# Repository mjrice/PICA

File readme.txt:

PICA

Power, Interface, and Control Adapter

An Arduino Mega shield for reprap machines

Based in part on RAMPS by Johnny Russell

Power

* 5x20mm replaceable fuse input 

* 12V to 24V input with on-board 12V buck converter for systems with both 24V and 12V devices

* Five separate MOSFET outputs:

1 High power (15A, up to 24V)
2 Medium power (6A, up to 24V)
2 Low power (2A, 12V)

* Plus 1 SSR output (SPST) capable of 240VAC/5A (more with heatsink)

Monitoring 

* four thermistor inputs
* six endstop inputs

Interface

* LCD interface (SMART LCD controller pinout)
* I2C, 2xSerial, 3xPWM, and auxiliary DC power output connections
* Five Pololu stepper motor driver sockets (A4988 or DRV8825)

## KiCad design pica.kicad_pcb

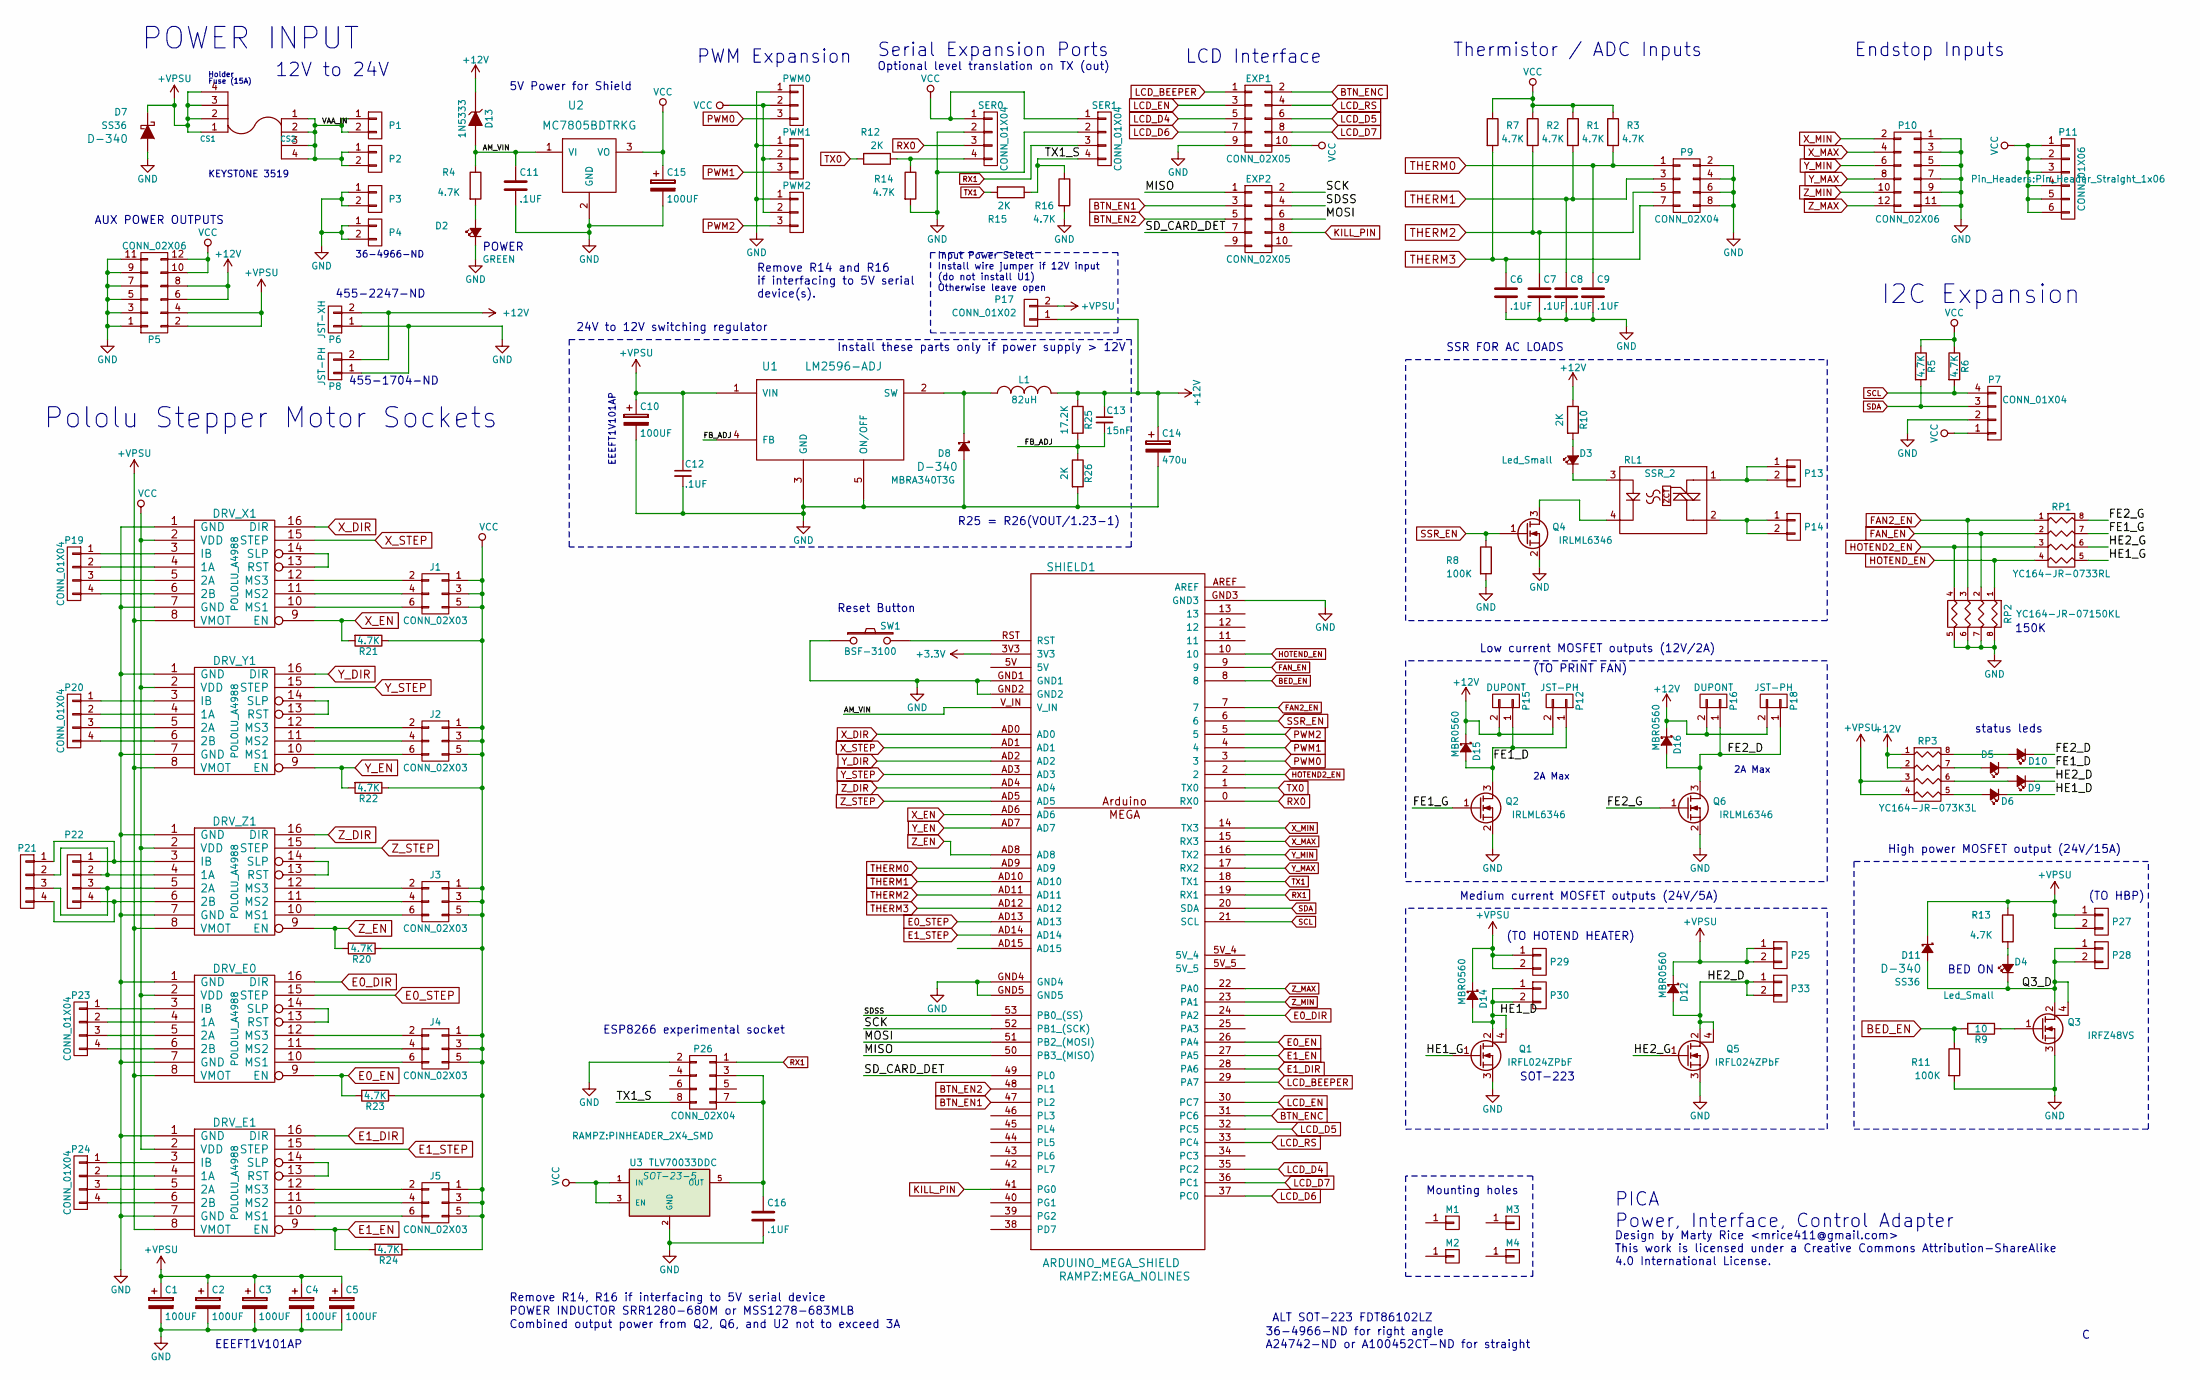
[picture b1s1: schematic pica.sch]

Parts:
C1, C2, C3, C4, C5, C10, C15: 100UF; c_elec_6.3x5.8
C6, C7, C8, C9, C11, C12, C16: .1UF; C_0805_HandSoldering
C13: 15nF; C_0805_HandSoldering
C14: 470u; C_Radial_D10_L13_P5
CS1, CS2: FUSE_CLIP_5x20; FUSE_CLIP_D_5x20
D2: GREEN; LED_1206
D3, D4, D5, D6, D9, D10: Led_Small; LED_1206
D7, D11: SS36; SMA_Handsoldering
D8: MBRA340T3G; SMA_Handsoldering
D12, D14, D15, D16: MBR0560; SOD-123
D13: 1N5333; Diode_Horizontal
DRV_E0, DRV_E1: POLOLU_A4988; SWDIP8_.6W
DRV_X1: POLOLU_A4988; SWDIP8_.6W
DRV_Y1: POLOLU_A4988; SWDIP8_.6W
DRV_Z1: POLOLU_A4988; SWDIP8_.6W
EXP1, EXP2: CONN_02X05; IDC_Header_Straight_10pins
J1, J2, J3, J4, J5: CONN_02X03; DIP-6_0_ELL
L1: 82uH; RH127
M1, M2, M3, M4: CONN_01X01; MHOLE125
P1, P2, P3, P4: 36-4966-ND; SPADE_CONN_RT
P5, P10: CONN_02X06; Pin_Header_Straight_2x06
P6: JST-XH; JST_XH_2POS
P7, P19, P20, P21, P22, P23, P24: CONN_01X04; Pin_Header_Straight_1x04
P8, P12, P18: JST-PH; JST_PH_2POS
P9: CONN_02X04; Pin_Header_Straight_2x04
P11: CONN_01X06; Pin_Header_Straight_1x06
P13, P14, P25, P27, P28, P29, P30, P33: CONN_01X02; SPACE_CONN_VERT
P15, P16: DUPONT; Pin_Header_Straight_1x02
P17: CONN_01X02; Pin_Header_Straight_1x02
P26: CONN_02X04; PINHEADER_2X4_SMD
PWM0, PWM1, PWM2: CONN_01X03; Pin_Header_Straight_1x03
Q1, Q5: IRFL024ZPbF; SOT-223
Q2, Q4, Q6: IRLML6346; SOT-23_Handsoldering
Q3: IRFZ48VS; TO-263-3Lead
R1, R2, R3, R4, R5, R6, R7, R13, R14, R16, R20, R21, R22, R23, R24: 4.7K; R_0805_HandSoldering
R8, R11: 100K; R_0805_HandSoldering
R9: 10; R_0805_HandSoldering
R10, R12, R15, R26: 2K; R_0805_HandSoldering
R25: 17.2K; R_0805_HandSoldering
RL1: SSR_2; I4-PAC
RP1: YC164-JR-0733RL; RESARY_4_CTS_744
RP2: YC164-JR-07150KL; RESARY_4_CTS_744
RP3: YC164-JR-073K3L; RESARY_4_CTS_744
SER0, SER1: CONN_01X04; Pin_Header_Straight_1x04
SHIELD1: ARDUINO_MEGA_SHIELD; MEGA_NOLINES
SW1: BSF-3100; BSF_RT
U1: LM2596-ADJ; TO-263-5Lead
U2: MC7805BDTRKG; TO-252-2Lead
U3: TLV70033DDC; SOT-23-5

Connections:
+3V3: SHIELD1.3V3
+12V: C13.1, C14.1, D13.1 (K), D15.1 (K), D16.1 (K), L1.2, P5.6, P5.8, P6.2, P8.2, P12.2, P15.2, P16.2, P17.1, P18.2, R10.1, R25.1, RP3.1, RP3.2
+VPSU: C1.1, C2.1, C3.1, C4.1, C5.1, C10.1, C12.1, CS1.1, CS1.2, CS1.3, CS1.4, D7.1 (K), D11.1 (K), D12.1 (K), D14.1 (K), DRV_E0.8 (VMOT), DRV_E1.8 (VMOT), DRV_X1.8 (VMOT), DRV_Y1.8 (VMOT), DRV_Z1.8 (VMOT), P5.2, P5.4, P17.2, P25.1, P25.2, P27.1, P27.2, P29.1, P29.2, R13.1, RP3.3, RP3.4, U1.1 (VIN)
/AM_VIN: C11.1, D13.2 (A), R4.1, SHIELD1.V_IN, U2.1 (VI)
/FB_ADJ: C13.2, R25.2, R26.1, U1.4 (FB)
/FE1_D: D5.1 (K), D15.2 (A), P12.1, P15.1, Q2.3 (D)
/FE1_G: Q2.1 (G), RP1.7 (R2)
/FE2_D: D10.1 (K), D16.2 (A), P16.1, P18.1, Q6.3 (D)
/FE2_G: Q6.1 (G), RP1.8 (R1)
/HE1_D: D6.1 (K), D14.2 (A), P30.1, P30.2, Q1.2 (D), Q1.4 (D)
/HE1_G: Q1.1 (G), RP1.5 (R4)
/HE2_D: D9.1 (K), D12.2 (A), P33.1, P33.2, Q5.2 (D), Q5.4 (D)
/HE2_G: Q5.1 (G), RP1.6 (R3)
/MISO: EXP2.1, SHIELD1.50 (PB3_(MISO))
/MOSI: EXP2.6, SHIELD1.51 (PB2_(MOSI))
/Q3_D: D4.1 (K), D11.2 (A), P28.1, P28.2, Q3.2 (D), Q3.4 (D)
/SCK: EXP2.2, SHIELD1.52 (PB1_(SCK))
/SDSS: EXP2.4, SHIELD1.53 (PB0_(SS))
/SD_CARD_DET: EXP2.7, SHIELD1.49 (PL0)
/TX1_S: P26.8, R15.1, R16.1, SER1.4
/VAA_IN: CS2.1, CS2.2, CS2.3, CS2.4, P1.1, P1.2, P2.1, P2.2
BED_EN: R9.2, R11.1, SHIELD1.8
BTN_EN1: EXP2.3, SHIELD1.47 (PL2)
BTN_EN2: EXP2.5, SHIELD1.48 (PL1)
BTN_ENC: EXP1.2, SHIELD1.31 (PC6)
E0_DIR: DRV_E0.16 (DIR), SHIELD1.24 (PA2)
E0_EN: DRV_E0.9 (EN), R23.2, SHIELD1.26 (PA4)
E0_STEP: DRV_E0.15 (STEP), SHIELD1.AD13
E1_DIR: DRV_E1.16 (DIR), SHIELD1.28 (PA6)
E1_EN: DRV_E1.9 (EN), R24.2, SHIELD1.27 (PA5)
E1_STEP: DRV_E1.15 (STEP), SHIELD1.AD14
FAN2_EN: RP1.1, RP2.3, SHIELD1.7
FAN_EN: RP1.2, RP2.2, SHIELD1.9
GND: C1.2, C2.2, C3.2, C4.2, C5.2, C6.2, C7.2, C8.2, C9.2, C10.2, C11.2, C12.2, C14.2, C15.2, C16.2, D2.1 (K), D7.2 (A), D8.2 (A), DRV_E0.1 (GND), DRV_E0.7 (GND), DRV_E1.1 (GND), DRV_E1.7 (GND), DRV_X1.1 (GND), DRV_X1.7 (GND), DRV_Y1.1 (GND), DRV_Y1.7 (GND), DRV_Z1.1 (GND), DRV_Z1.7 (GND), EXP1.9, P3.1, P3.2, P4.1, P4.2, P5.1, P5.3, P5.5, P5.7, P5.9, P5.11, P6.1, P7.2, P8.1, P9.2, P9.4, P9.6, P9.8, P10.1, P10.3, P10.5, P10.7, P10.9, P10.11, P26.2, PWM0.1, PWM1.1, PWM2.1, Q1.3 (S), Q2.2 (S), Q3.3 (S), Q4.2 (S), Q5.3 (S), Q6.2 (S), R8.2, R11.2, R14.2, R16.2, R26.2, RP2.5 (R4), RP2.6 (R3), RP2.7 (R2), RP2.8 (R1), SER0.2, SER1.2, SHIELD1.GND1, SHIELD1.GND2, SHIELD1.GND3, SHIELD1.GND4, SHIELD1.GND5, SW1.1, U1.3 (GND), U1.5 (ON/OFF), U2.2 (GND), U3.2 (GND)
HOTEND2_EN: RP1.3, RP2.4, SHIELD1.2
HOTEND_EN: RP1.4, RP2.1, SHIELD1.10
KILL_PIN: EXP2.8, SHIELD1.41 (PG0)
LCD_BEEPER: EXP1.1, SHIELD1.29 (PA7)
LCD_D4: EXP1.5, SHIELD1.35 (PC2)
LCD_D5: EXP1.6, SHIELD1.32 (PC5)
LCD_D6: EXP1.7, SHIELD1.37 (PC0)
LCD_D7: EXP1.8, SHIELD1.36 (PC1)
LCD_EN: EXP1.3, SHIELD1.30 (PC7)
LCD_RS: EXP1.4, SHIELD1.33 (PC4)
unnamed: C16.1, P26.3, P26.7, U3.5 (OUT)
unnamed: D2.2 (A), R4.2
unnamed: D3.1 (K), RL1.3
unnamed: D3.2 (A), R10.2
unnamed: D4.2 (A), R13.2
unnamed: D5.2 (A), RP3.7 (R2)
unnamed: D6.2 (A), RP3.5 (R4)
unnamed: D8.1 (K), L1.1, U1.2 (SW)
unnamed: D9.2 (A), RP3.6 (R3)
unnamed: D10.2 (A), RP3.8 (R1)
unnamed: DRV_E0.3 (IB), P23.1
unnamed: DRV_E0.4 (1A), P23.2
unnamed: DRV_E0.5 (2A), P23.3
unnamed: DRV_E0.6 (2B), P23.4
unnamed: DRV_E0.10 (MS1), J4.6
unnamed: DRV_E0.11 (MS2), J4.4
unnamed: DRV_E0.12 (MS3), J4.2
unnamed: DRV_E0.13 (RST), DRV_E0.14 (SLP)
unnamed: DRV_E1.3 (IB), P24.1
unnamed: DRV_E1.4 (1A), P24.2
unnamed: DRV_E1.5 (2A), P24.3
unnamed: DRV_E1.6 (2B), P24.4
unnamed: DRV_E1.10 (MS1), J5.6
unnamed: DRV_E1.11 (MS2), J5.4
unnamed: DRV_E1.12 (MS3), J5.2
unnamed: DRV_E1.13 (RST), DRV_E1.14 (SLP)
unnamed: DRV_X1.3 (IB), P19.1
unnamed: DRV_X1.4 (1A), P19.2
unnamed: DRV_X1.5 (2A), P19.3
unnamed: DRV_X1.6 (2B), P19.4
unnamed: DRV_X1.10 (MS1), J1.6
unnamed: DRV_X1.11 (MS2), J1.4
unnamed: DRV_X1.12 (MS3), J1.2
unnamed: DRV_X1.13 (RST), DRV_X1.14 (SLP)
unnamed: DRV_Y1.3 (IB), P20.1
unnamed: DRV_Y1.4 (1A), P20.2
unnamed: DRV_Y1.5 (2A), P20.3
unnamed: DRV_Y1.6 (2B), P20.4
unnamed: DRV_Y1.10 (MS1), J2.6
unnamed: DRV_Y1.11 (MS2), J2.4
unnamed: DRV_Y1.12 (MS3), J2.2
unnamed: DRV_Y1.13 (RST), DRV_Y1.14 (SLP)
unnamed: DRV_Z1.3 (IB), P21.1, P22.1
unnamed: DRV_Z1.4 (1A), P21.2, P22.2
unnamed: DRV_Z1.5 (2A), P21.3, P22.3
unnamed: DRV_Z1.6 (2B), P21.4, P22.4
unnamed: DRV_Z1.10 (MS1), J3.6
unnamed: DRV_Z1.11 (MS2), J3.4
unnamed: DRV_Z1.12 (MS3), J3.2
unnamed: DRV_Z1.13 (RST), DRV_Z1.14 (SLP)
unnamed: P13.1, P13.2, RL1.1
unnamed: P14.1, P14.2, RL1.2
unnamed: Q3.1 (G), R9.1
unnamed: Q4.3 (D), RL1.4
unnamed: R12.1, R14.1, SER0.4
unnamed: SHIELD1.RST, SW1.2
PWM0: PWM0.3, SHIELD1.3
PWM1: PWM1.3, SHIELD1.4
PWM2: PWM2.3, SHIELD1.5
RX0: SER0.3, SHIELD1.0 (RX0)
RX1: P26.1, SER1.3, SHIELD1.19 (RX1)
SCL: P7.4, R6.2, SHIELD1.21 (SCL)
SDA: P7.3, R5.2, SHIELD1.20 (SDA)
SSR_EN: Q4.1 (G), R8.1, SHIELD1.6
THERM0: C9.1, P9.1, R3.2, SHIELD1.AD9
THERM1: C8.1, P9.3, R1.2, SHIELD1.AD10
THERM2: C7.1, P9.5, R2.2, SHIELD1.AD11
THERM3: C6.1, P9.7, R7.2, SHIELD1.AD12
TX0: R12.2, SHIELD1.1 (TX0)
TX1: R15.2, SHIELD1.18 (TX1)
VCC: C15.1, DRV_E0.2 (VDD), DRV_E1.2 (VDD), DRV_X1.2 (VDD), DRV_Y1.2 (VDD), DRV_Z1.2 (VDD), EXP1.10, J1.1, J1.3, J1.5, J2.1, J2.3, J2.5, J3.1, J3.3, J3.5, J4.1, J4.3, J4.5, J5.1, J5.3, J5.5, P5.10, P5.12, P7.1, P11.1, P11.2, P11.3, P11.4, P11.5, P11.6, PWM0.2, PWM1.2, PWM2.2, R1.1, R2.1, R3.1, R5.1, R6.1, R7.1, R20.1, R21.1, R22.1, R23.1, R24.1, SER0.1, SER1.1, U2.3 (VO), U3.1 (IN), U3.3 (EN)
X_DIR: DRV_X1.16 (DIR), SHIELD1.AD0
X_EN: DRV_X1.9 (EN), R21.2, SHIELD1.AD6
X_MAX: P10.4, SHIELD1.15 (RX3)
X_MIN: P10.2, SHIELD1.14 (TX3)
X_STEP: DRV_X1.15 (STEP), SHIELD1.AD1
Y_DIR: DRV_Y1.16 (DIR), SHIELD1.AD2
Y_EN: DRV_Y1.9 (EN), R22.2, SHIELD1.AD7
Y_MAX: P10.8, SHIELD1.17 (RX2)
Y_MIN: P10.6, SHIELD1.16 (TX2)
Y_STEP: DRV_Y1.15 (STEP), SHIELD1.AD3
Z_DIR: DRV_Z1.16 (DIR), SHIELD1.AD4
Z_EN: DRV_Z1.9 (EN), R20.2, SHIELD1.AD8
Z_MAX: P10.12, SHIELD1.22 (PA0)
Z_MIN: P10.10, SHIELD1.23 (PA1)
Z_STEP: DRV_Z1.15 (STEP), SHIELD1.AD5

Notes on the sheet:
POWER INPUT
(TO HBP)
(TO PRINT FAN)
(TO HOTEND HEATER)
EEEFT1V101AP
POWER
BED ON
I2C Expansion
Holder
Fuse (15A)
Endstop Inputs
Thermistor / ADC Inputs
LCD Interface
Pololu Stepper Motor Sockets
2A Max
Serial Expansion Ports
PICA Power, Interface, Control Adapter
12V to 24V
PWM Expansion
Input Power Select Install wire jumper if 12V input (do not install U1) Otherwise leave open
36-4966-ND
SOT-223
Low current MOSFET outputs (12V/2A)
36-4966-ND for right angle A24742-ND or A100452CT-ND for straight
Medium current MOSFET outputs (24V/5A)
High power MOSFET output (24V/15A)
150K
AUX POWER OUTPUTS
ALT SOT-223 FDT86102LZ
SSR FOR AC LOADS
Mounting holes
Combined output power from Q2, Q6, and U2 not to exceed 3A
Reset Button
5V Power for Shield
status leds
24V to 12V switching regulator
R25 = R26(VOUT/1.23-1)
Install these parts only if power supply > 12V
POWER INDUCTOR SRR1280-680M or MSS1278-683MLB
Optional level translation on TX (out)

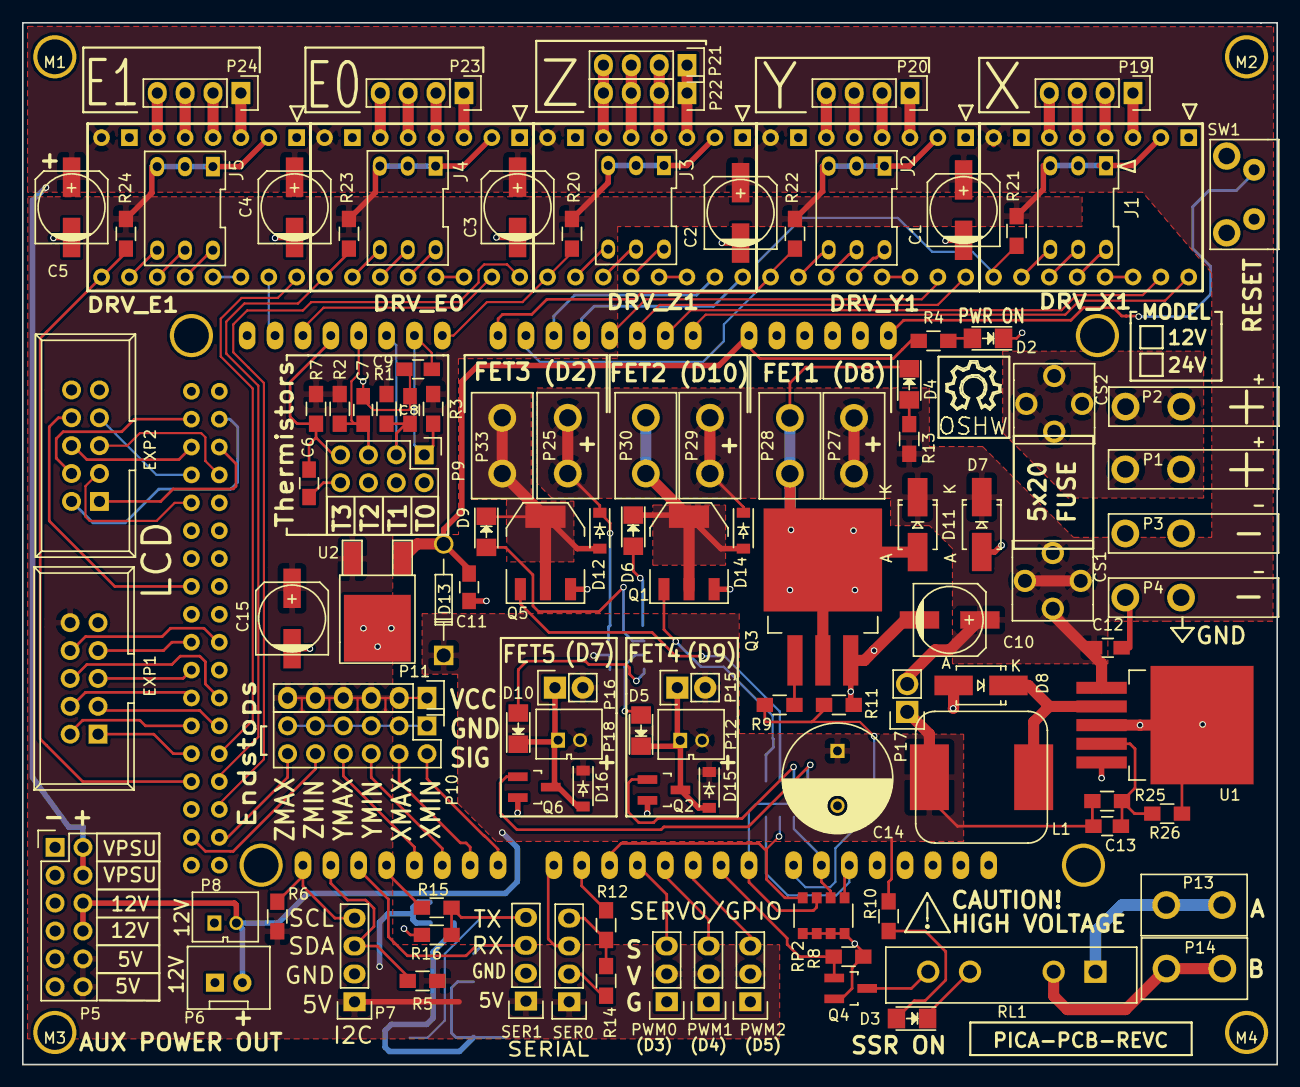
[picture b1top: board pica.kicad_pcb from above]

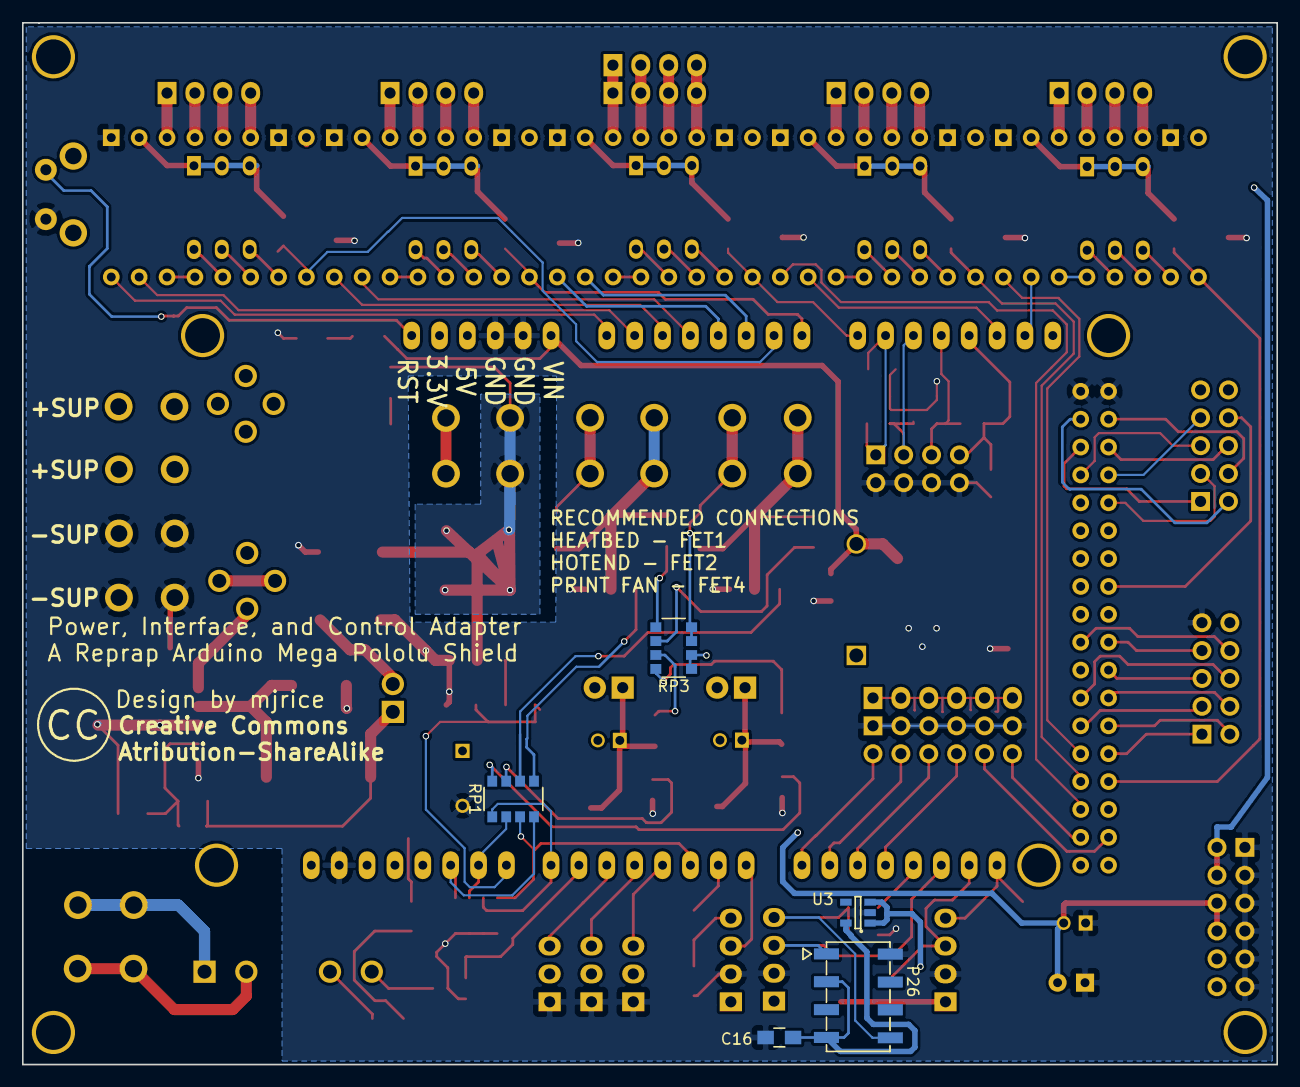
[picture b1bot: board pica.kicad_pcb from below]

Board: 2 copper layers, 114.3 x 94.9 mm, 124 parts (5 on the bottom side), 129 nets.

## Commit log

2016-04-09 :lollipop: Added .gitattributes & .gitignore files
2016-04-09 added pdf of schematic
2016-04-09 added png image of the board layout
2016-04-30 rev b
2016-05-26 added assembly guide
2016-06-04 Final rev C design files
2017-01-24 assembly guide for rev C
2017-04-17 update rev e files

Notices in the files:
pica.kicad_pcb:
Creative Commons
Atribution-ShareAlike
pica.sch:
This work is licensed under a Creative Commons Attribution-ShareAlike
